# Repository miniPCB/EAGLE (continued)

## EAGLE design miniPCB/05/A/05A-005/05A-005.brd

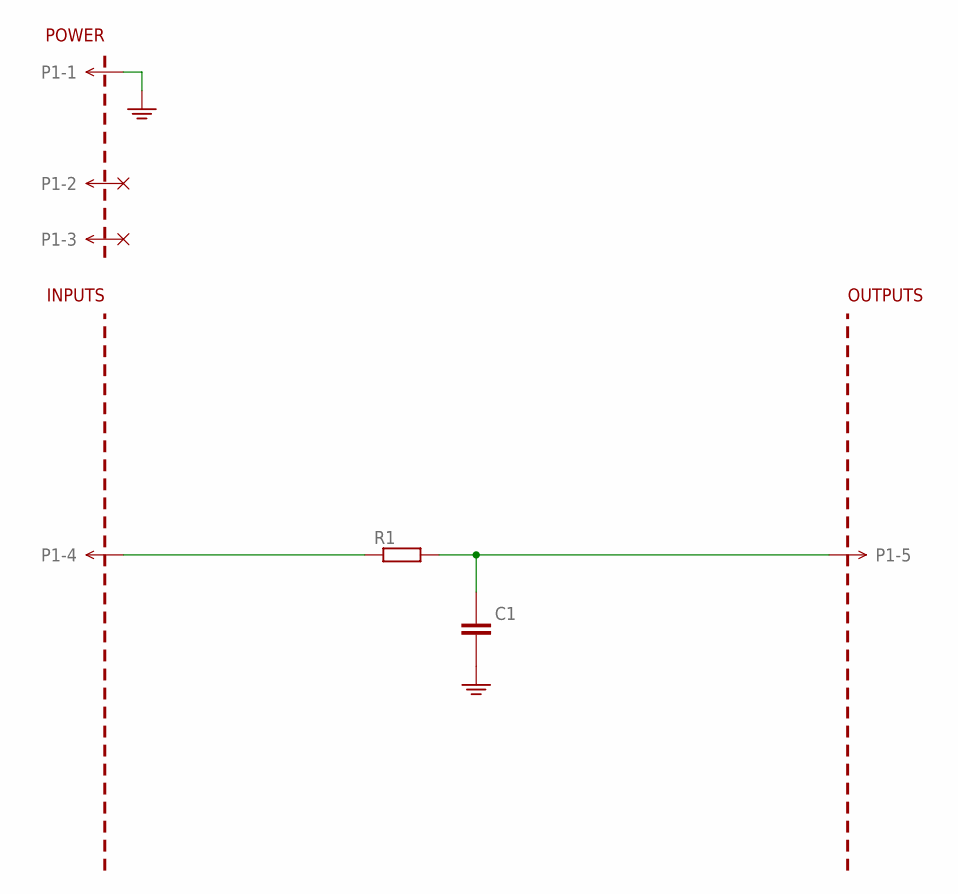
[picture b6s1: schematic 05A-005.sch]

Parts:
C1: CAPACITORTHD; C050-024X044
P1: MINIPCB_5P5P; PINS_1X5
PCB1: MINIPCB_0P00A-20X25; MINIPCB_00A_20X25
R1: RESISTORTHD; 0204/10

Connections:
GND: C1.2 (-), P1.1
unnamed: C1.1 (+), P1.5, R1.2
unnamed: P1.4, R1.1

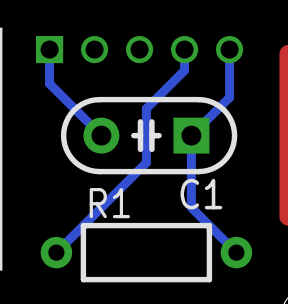
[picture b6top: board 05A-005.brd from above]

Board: 2 copper layers, 4 parts (0 on the bottom side), 3 nets.

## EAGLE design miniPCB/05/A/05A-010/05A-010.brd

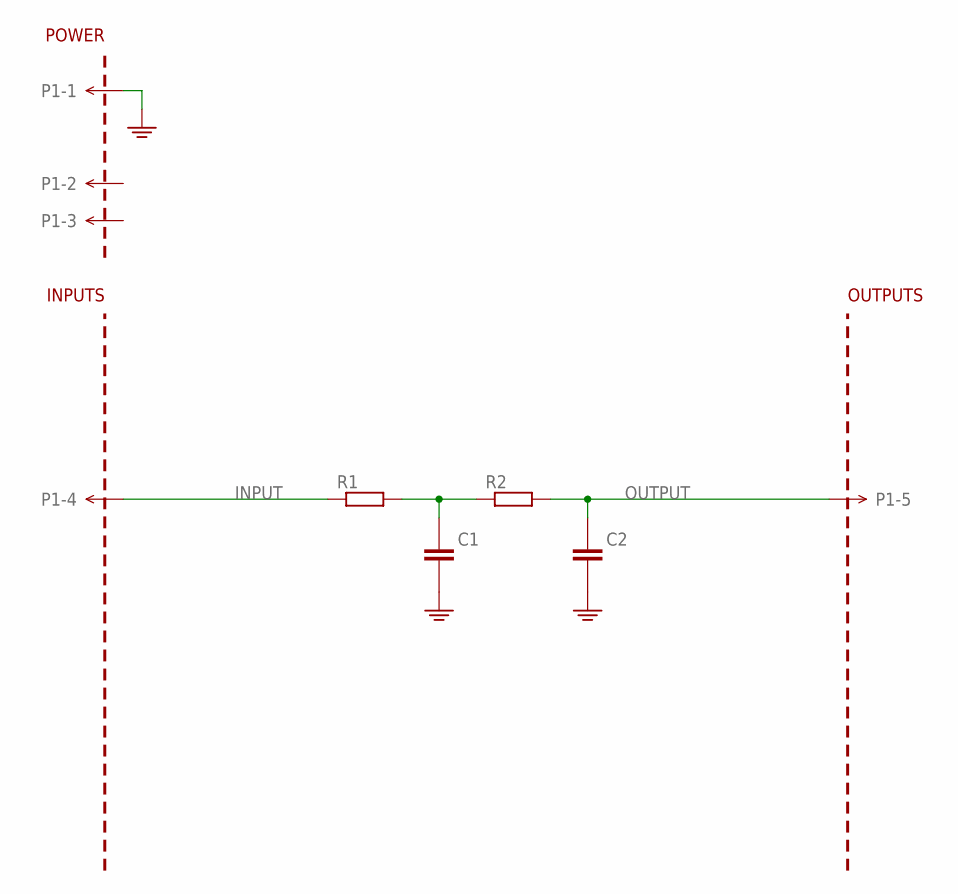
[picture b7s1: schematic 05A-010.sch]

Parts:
C1, C2: CAPACITORTHD; C050-024X044
P1: MINIPCB_5P5P; PINS_1X5
PCB1: MINIPCB_0P00A-20X33; MINIPCB_00A_20X33
R1, R2: RESISTORTHD; 0204/10

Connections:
GND: C1.2 (-), C2.2 (-), P1.1
unnamed: P1.4, R1.1
unnamed: C1.1 (+), R1.2, R2.1
unnamed: C2.1 (+), P1.5, R2.2

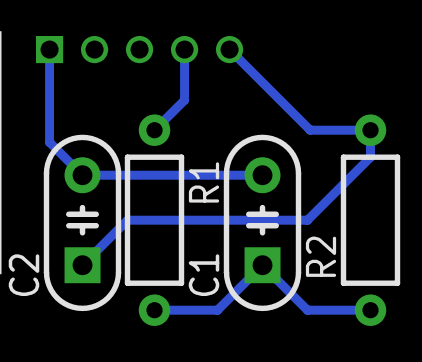
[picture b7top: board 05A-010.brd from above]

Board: 2 copper layers, 6 parts (0 on the bottom side), 4 nets.

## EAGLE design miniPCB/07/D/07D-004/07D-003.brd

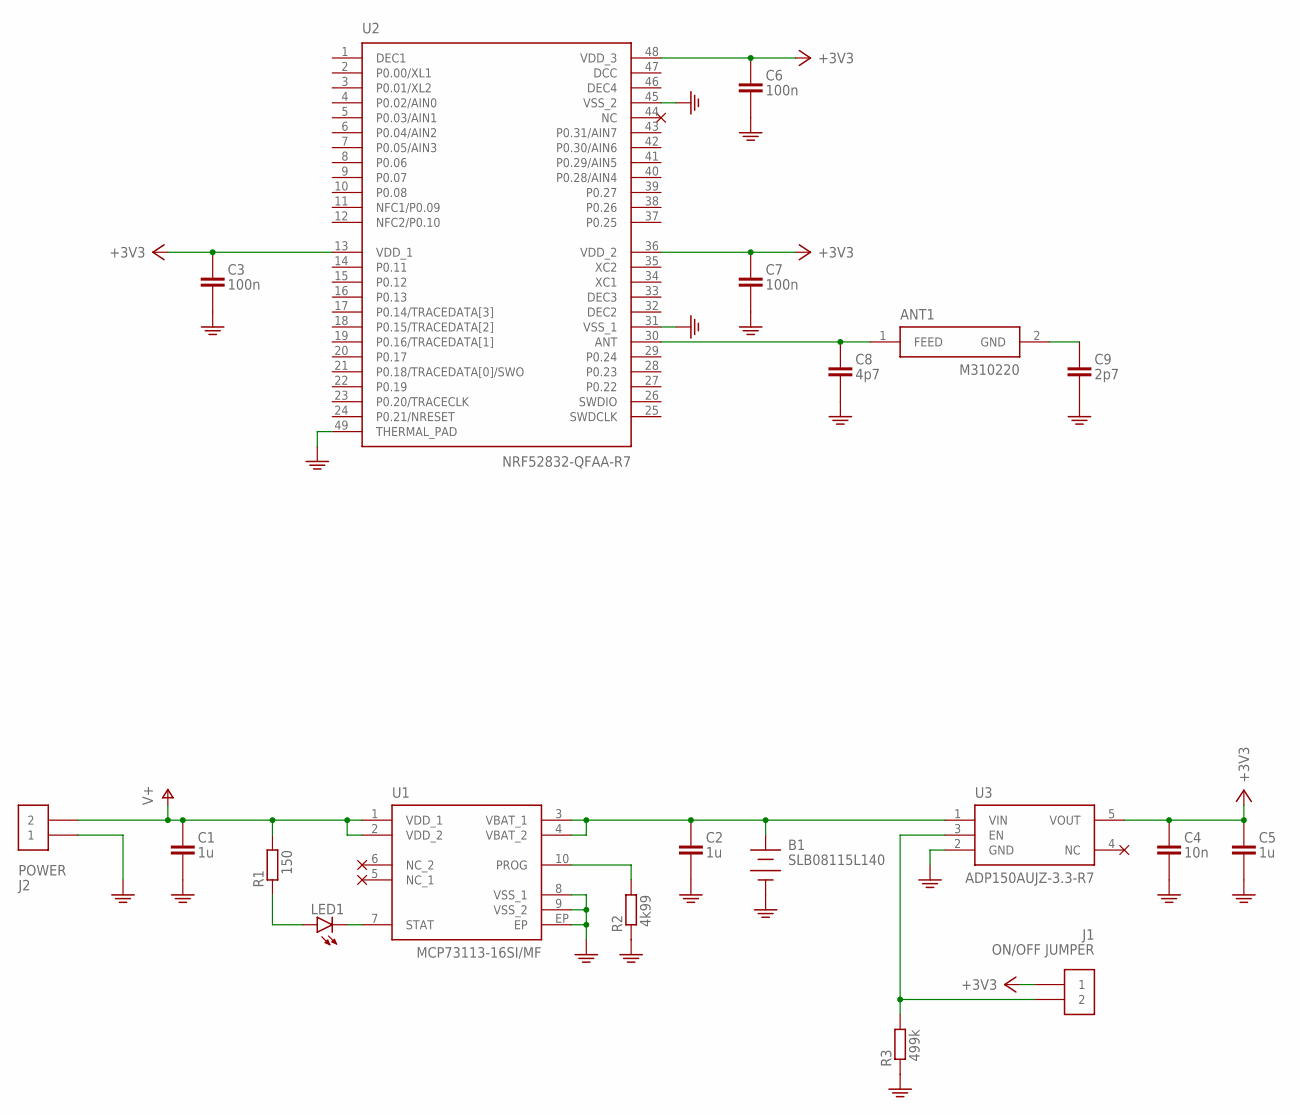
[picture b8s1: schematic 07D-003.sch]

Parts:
ANT1: M310220
B1: SLB08115L140; BATTERY_SLB08115L140
C1, C2, C5: 1u; C0402
C3, C6, C7: 100n; C0402
C4: 10n; C0402
C8: 4p7; C0402
C9: 2p7; C0402
J1: ON/OFF JUMPER; PINS_2
J2: POWER; PINS_2
LED1: LEDSML0603; SML0603
R1: 150; R0402
R2: 4k99; R0402
R3: 499k; R0402
U1: MCP73113-16SI/MF; DFN-10
U2: NRF52832-QFAA-R7; QFN40P600X600X90-49N
U3: ADP150AUJZ-3.3-R7; SOT25

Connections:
+3V3: C3.1 (+), C4.1 (+), C5.1 (+), C6.1 (+), C7.1 (+), J1.1, U2.13 (VDD_1), U2.36 (VDD_2), U2.48 (VDD_3), U3.5 (VOUT)
ANTFEED: ANT1.1 (FEED), C8.1 (+), U2.30 (ANT)
ANTGND: ANT1.2 (GND), C9.1 (+)
B+: B1.1+ (+), C2.1 (+), U1.3 (VBAT_1), U1.4 (VBAT_2), U3.1 (VIN)
ENABLE: J1.2, R3.2, U3.3 (EN)
GND: B1.2- (-), C1.2 (-), C2.2 (-), C3.2 (-), C4.2 (-), C5.2 (-), C6.2 (-), C7.2 (-), C8.2 (-), C9.2 (-), J2.1, R2.1, R3.1, U1.8 (VSS_1), U1.9 (VSS_2), U1.EP, U2.31 (VSS_1), U2.45 (VSS_2), U2.49 (THERMAL_PAD), U3.2 (GND)
LED+: LED1.A, R1.1
PROG: R2.2, U1.10 (PROG)
STAT: LED1.C, U1.7 (STAT)
V+: C1.1 (+), J2.2, R1.2, U1.1 (VDD_1), U1.2 (VDD_2)

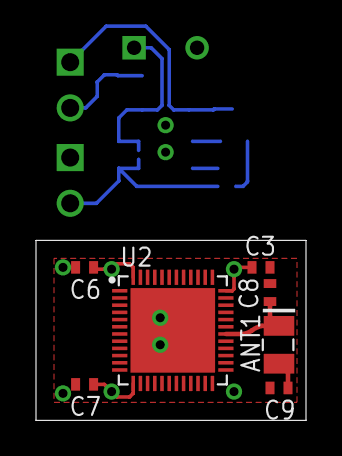
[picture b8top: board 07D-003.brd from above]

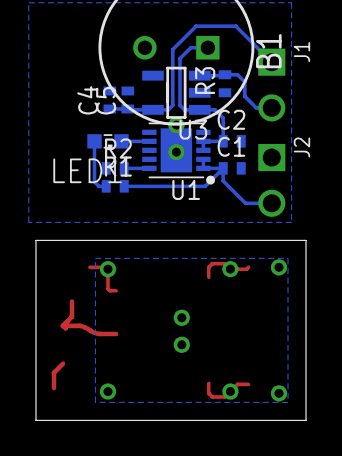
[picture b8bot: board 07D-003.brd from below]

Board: 6 copper layers, 15.0 x 10.0 mm, 20 parts (13 on the bottom side), 10 nets.
